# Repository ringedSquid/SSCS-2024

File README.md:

# SSCS-2024 
SSCS 2024 Contest entry <br>
[Project Video](https://www.youtube.com/watch?v=Hh_UeHd2Llg&t=2s)

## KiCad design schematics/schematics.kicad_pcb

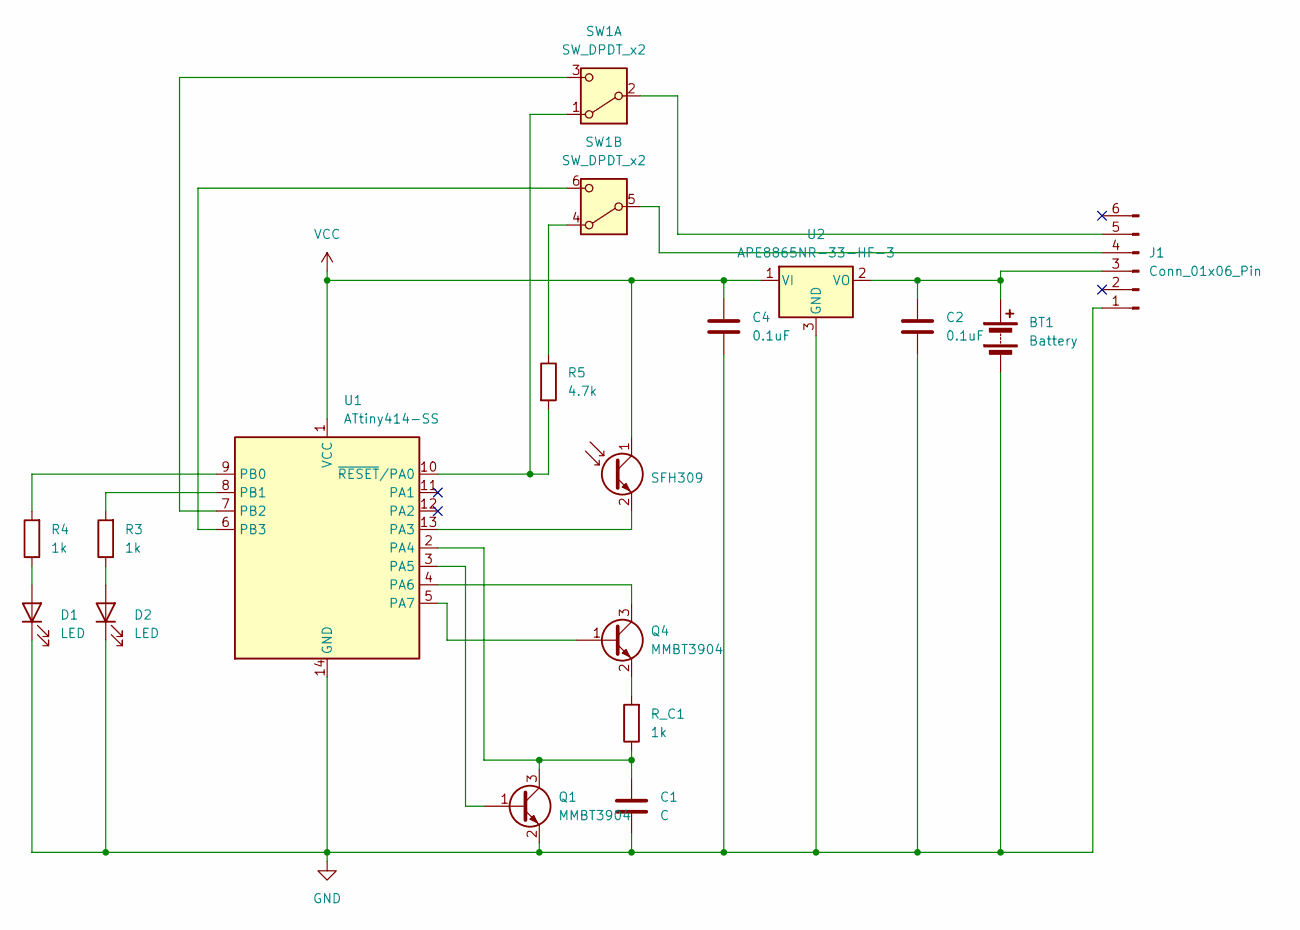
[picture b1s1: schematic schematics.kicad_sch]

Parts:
BT1: Battery; BatteryHolder_MPD_BH-18650-PC2
C1: C; CP_Radial_D5.0mm_P2.00mm
C2, C4: 0.1uF; C_0805_2012Metric_Pad1.18x1.45mm_HandSolder
D1, D2: LED; LED_D3.0mm_Horizontal_O1.27mm_Z2.0mm
J1: Conn_01x06_Pin; PinHeader_1x06_P2.54mm_Vertical
Q1, Q4: MMBT3904; SOT-23
Q3: SFH309; LED_D3.0mm_Horizontal_O1.27mm_Z2.0mm
R3, R4: 1k; R_0603_1608Metric_Pad0.98x0.95mm_HandSolder
R5: 4.7k; R_0603_1608Metric_Pad0.98x0.95mm_HandSolder
R_C1: 1k; R_Axial_DIN0207_L6.3mm_D2.5mm_P2.54mm_Vertical
SW1: SW_DPDT_x2; SW_DPDT_CK_JS202011JCQN
U1: ATtiny414-SS; SOIC-14_3.9x8.7mm_P1.27mm
U2: APE8865NR-33-HF-3; SOT-23

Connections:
GND: BT1.2 (-), C1.2, C2.2, C4.2, D1.1 (K), D2.1 (K), J1.1, Q1.2 (E), U1.14 (GND), U2.3 (GND); also elsewhere on the board
unnamed 1: BT1.1 (+), C2.1, J1.3, U2.2 (VO); also elsewhere on the board
unnamed: D1.2 (A), R4.1
unnamed: D2.2 (A), R3.1
unnamed: J1.4, SW1.5 (B)
unnamed: J1.5, SW1.2 (B)
unnamed: Q1.1 (B), U1.3 (PA5)
unnamed: C1.1, Q1.3 (C), R_C1.1, U1.2 (PA4)
unnamed: Q3.2 (E), U1.13 (PA3)
unnamed: Q4.1 (B), U1.5 (PA7)
unnamed: Q4.3 (C), U1.4 (PA6)
unnamed: Q4.2 (E), R_C1.2
unnamed: R5.2, SW1.1 (A), U1.10 (~RESET/PA0)
unnamed: SW1.3 (C), U1.7 (PB2)
unnamed: R5.1, SW1.4 (A)
unnamed: SW1.6 (C), U1.6 (PB3)
unnamed: R4.2, U1.9 (PB0)
unnamed: R3.2, U1.8 (PB1)
VCC: C4.1, Q3.1 (C), U1.1 (VCC), U2.1 (VI); also elsewhere on the board

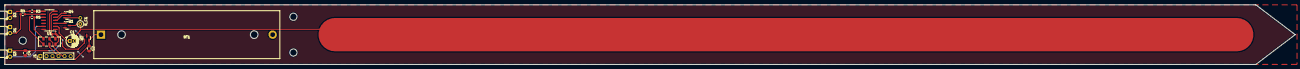
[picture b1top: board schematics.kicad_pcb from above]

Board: 2 copper layers, 541.0 x 25.0 mm, 17 parts (0 on the bottom side), 19 nets.

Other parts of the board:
Q5: APE8865NR-33-HF-3; SOT-23

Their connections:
GND: Q5.3 (GND); also elsewhere on the board
unnamed 1: Q5.2 (VO); also elsewhere on the board
VCC: Q5.1 (VI); also elsewhere on the board

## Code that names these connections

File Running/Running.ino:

#include <avr/sleep.h>

//Pinout
#define DAC_OUT PIN_PA6
#define DISCHARGE PIN_PA5
#define CHARGE PIN_PA7
#define ADC_IN PIN_PA4

#define PTN_IN PIN_PA2
#define RED_LED PIN_PB1
#define GRN_LED PIN_PB0

#define AVERAGE_RES 20

//Coefficients for linear model
#define DRY 620.0
#define WET 30.0

//user defined moisture ranges (acceptable range)
#define RL 0.3
#define RH 0.7

double M = 0;
double B = 0;

void setup() {
  set_sleep_mode(SLEEP_MODE_PWR_DOWN);
  sleep_enable();

  Serial.begin(57600);
  DACReference(INTERNAL1V5);
  analogReference(INTERNAL1V5);

  M = 1/(WET-DRY);
  B = -DRY*M;

  //init used pin modes
  pinMode(ADC_IN, INPUT);
  pinMode(PTN_IN, INPUT);

  pinMode(RED_LED, OUTPUT);
  pinMode(GRN_LED, OUTPUT);
  pinMode(DAC_OUT, OUTPUT);
  pinMode(CHARGE, OUTPUT);
  pinMode(DISCHARGE, OUTPUT);

  //init other pins
  pinMode(PIN_PB3, OUTPUT);
  pinMode(PIN_PB2, OUTPUT);
  pinMode(PIN_PA3, OUTPUT);
  pinMode(PIN_PA1, OUTPUT);
  pinMode(PIN_PA0, OUTPUT);

  //init pin states
  digitalWrite(CHARGE, LOW);
  digitalWrite(DISCHARGE, LOW);
  digitalWrite(GRN_LED, LOW);
  digitalWrite(RED_LED, LOW);
  analogWrite(DAC_OUT, 0);

}

void loop() {
  double moistureLevel = getMoistureLevel(getRawData());
  //Serial.println(moistureLevel, 8);
  //Serial.println(M, 8);
  if (moistureLevel <= RL) {
    digitalWrite(RED_LED, HIGH);
  }
  else if (moistureLevel >= RH) {
    digitalWrite(GRN_LED, HIGH);
    digitalWrite(RED_LED, HIGH);
  }
  else {
    digitalWrite(GRN_LED, HIGH);
  }
  delay(5000);
  sleep();
}

void sleep() {
  digitalWrite(DISCHARGE, HIGH);
  digitalWrite(CHARGE, LOW);
  digitalWrite(GRN_LED, LOW);
  digitalWrite(RED_LED, LOW);
  analogWrite(DAC_OUT, 0);                                                                                                                                                                                                                                                                                                                                                                                                           
  //Disable ADC
  ADC0.CTRLA &= ~ADC_ENABLE_bm;
  //Interrupt on rising
  PORTA.PIN2CTRL = 0b00000010;
  set_sleep_mode(SLEEP_MODE_PWR_DOWN);
  sleep_enable();
  sleep_cpu();
}

ISR(PORTA_PORT_vect) {
  //Clear flags
  PORTA.INTFLAGS = 255;
  //Disable interrupt
  PORTA.PIN2CTRL &= ~(0b00000111);
  //enable ADC
  ADC0.CTRLA |= ADC_ENABLE_bm;
}

double getMoistureLevel(double x) {
  return M * x + B;
}

double getRawData() {
  double sum = 0;
  analogWrite(DAC_OUT, 255);
  delay(10);
  for (int i = 0; i < AVERAGE_RES; i++) {
     digitalWrite(CHARGE, HIGH);
     digitalWrite(DISCHARGE, LOW);
     int val = analogRead(ADC_IN);
     digitalWrite(CHARGE, LOW);
     digitalWrite(DISCHARGE, HIGH);
     sum += val;
     delay(10);     
  }
  //Serial.println(sum/AVERAGE_RES);
  return sum/AVERAGE_RES;   
}

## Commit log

2024-07-06 schematics
2024-07-16 dacref() problems
2024-07-19 PCB ordered
2024-07-26 RC_TEST
2024-07-26 started new stuff
2024-07-27 working on interrupts
2024-07-28 ISR complete
2024-07-28 interrupts debugging
2024-07-31 rise time working
2025-08-23 images
